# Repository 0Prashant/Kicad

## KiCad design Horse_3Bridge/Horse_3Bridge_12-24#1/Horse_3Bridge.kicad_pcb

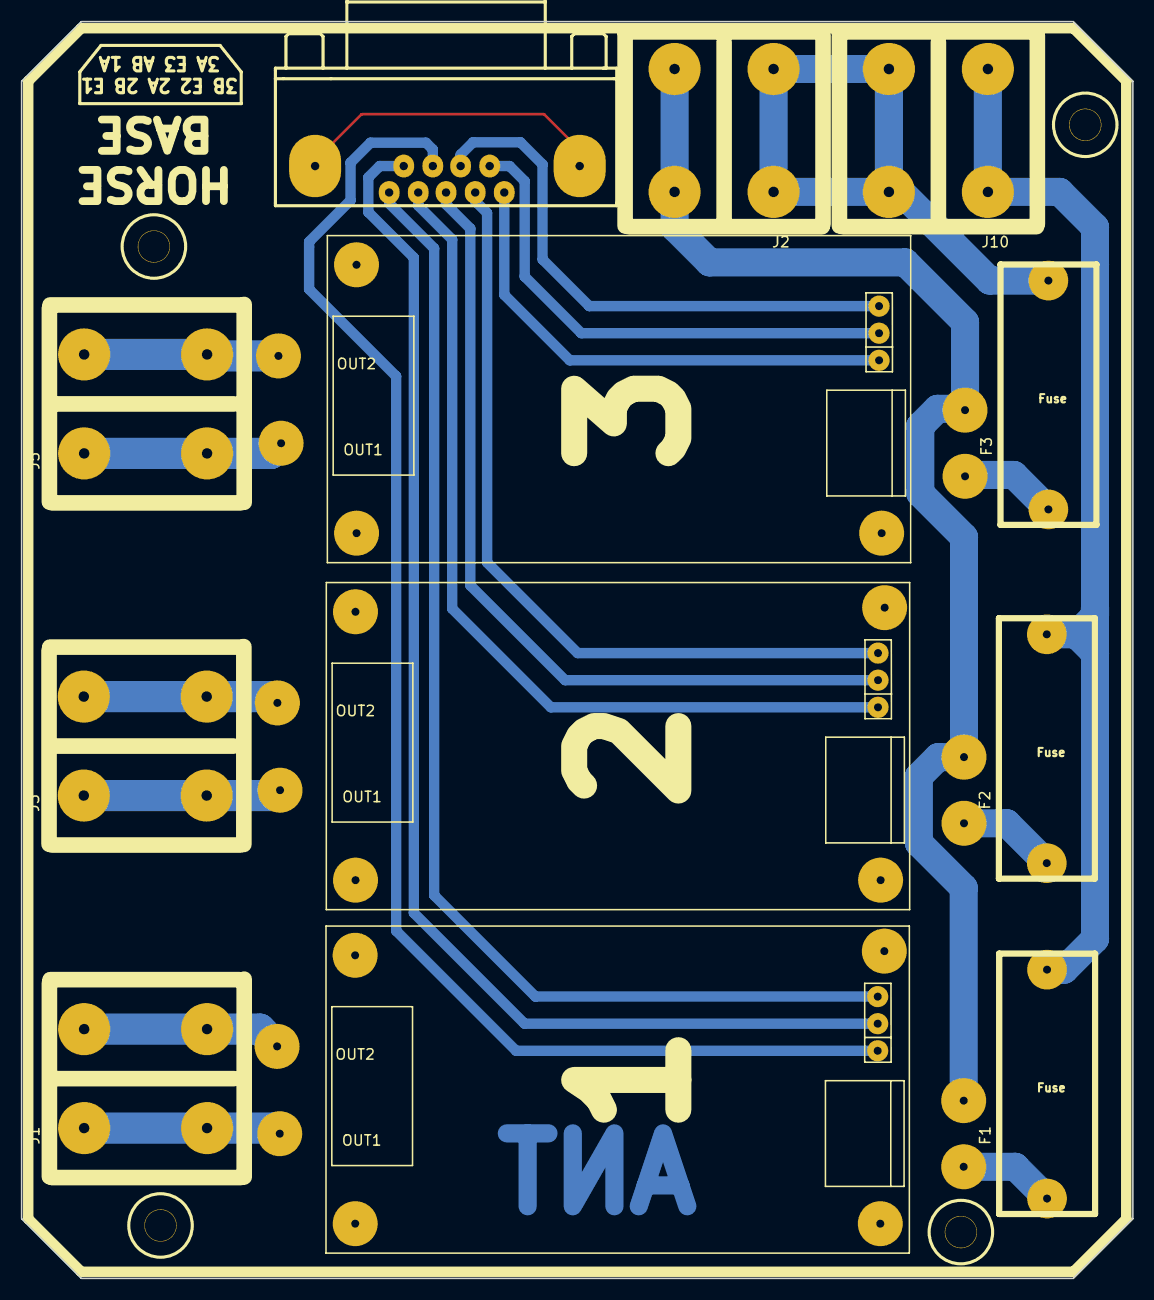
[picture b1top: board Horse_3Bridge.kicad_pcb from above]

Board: 2 copper layers, 106.7 x 120.7 mm, 16 parts (0 on the bottom side), 21 nets.

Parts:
F1, F2, F3: Fuse; Fuse_Holder
J1: M1; Solar_Connector
J2, J10: Power; Solar_Connector
J3: M2; Solar_Connector
J4: DB9_Female_MountingHoles; Connector_DB_9
J5: M3; Solar_Connector
J6, J7, J8, J9: Bolt; Nut_Bolt
U1: Motor_Driver1; H_Bridge
U2: Motor_Driver2; H_Bridge
U3: Motor_Driver3; H_Bridge

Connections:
+12V: F1.1, F2.1, J10.1
/EN1: J4.1, U1.3
/EN2: J4.4, U2.3
/EN3: J4.8, U3.3
/I1A: J4.6, U1.4
/I1B: J4.7, U1.5
/I2A: J4.3, U2.4
/I2B: J4.2, U2.5
/I3A: J4.9, U3.4
/I3B: J4.5, U3.5
/V: F3.1, J2.1, J10.2
GND: J2.2, U1.7, U2.7, U3.7
unnamed: F1.2, U1.6
unnamed: F2.2, U2.6
unnamed: F3.2, U3.6
unnamed: J1.1, U1.1
unnamed: J1.2, U1.2
unnamed: J3.1, U2.1
unnamed: J3.2, U2.2
unnamed: J5.1, U3.1
unnamed: J5.2, U3.2

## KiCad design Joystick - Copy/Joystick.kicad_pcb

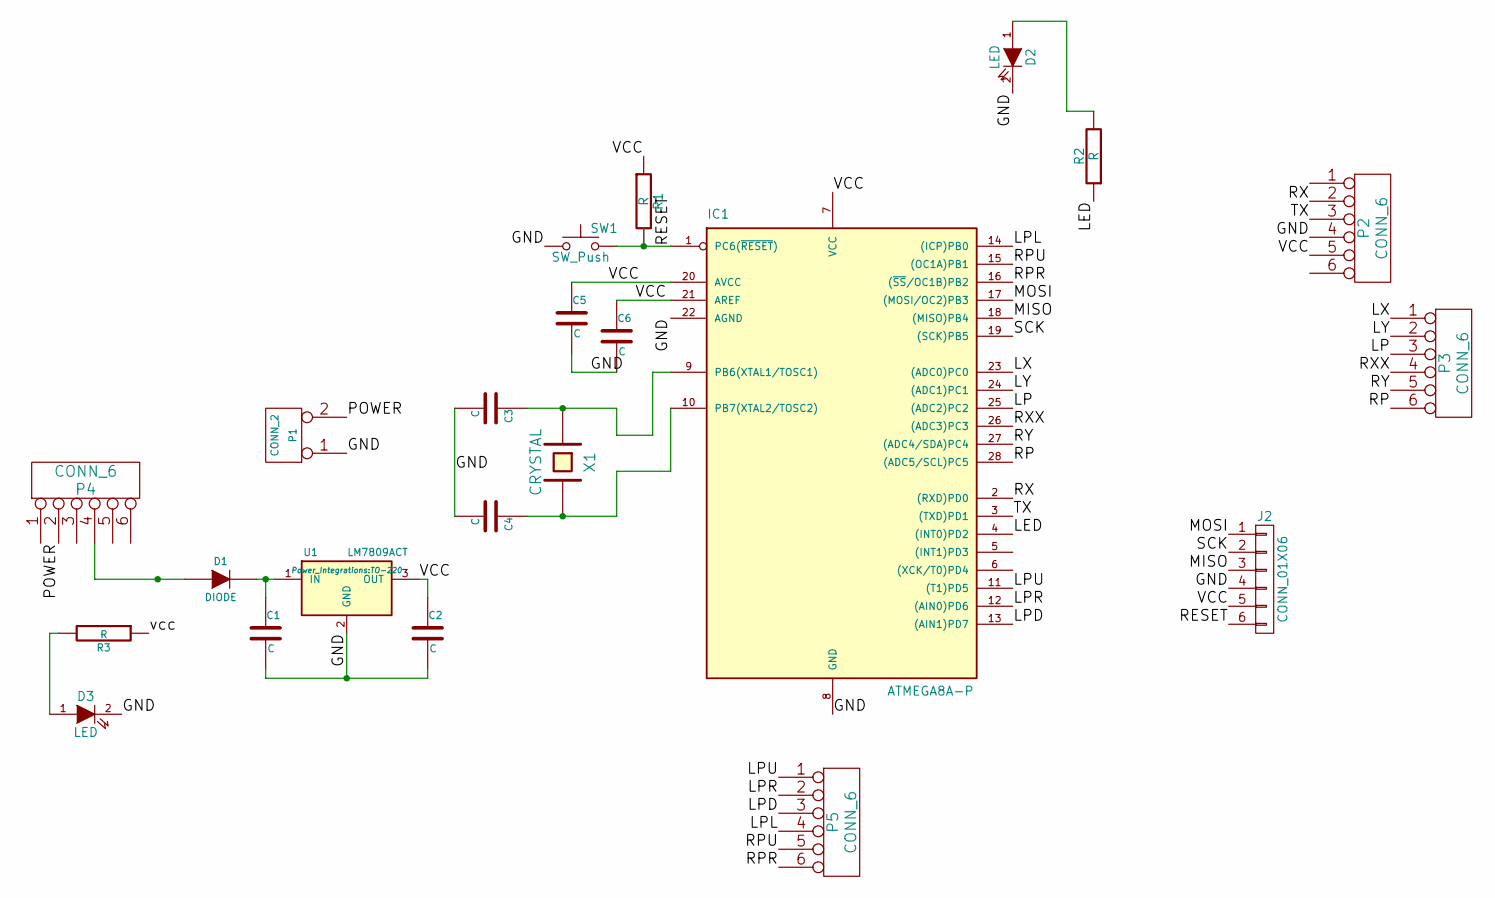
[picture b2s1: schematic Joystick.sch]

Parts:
C1: C; CP_Radial_Tantal_D4.5mm_P2.50mm
C2: C; CP_Radial_Tantal_D5.0mm_P2.50mm
C3, C4, C5, C6: C; C_Disc_D5.0mm_W2.5mm_P2.50mm
D1: DIODE; D_DO-41_SOD81_P10.16mm_Horizontal
D2, D3: LED; LED_D3.0mm
IC1: ATMEGA8A-P; DIP-28_W7.62mm
J2: CONN_01X06; Pin_Header_Straight_1x06_Pitch2.54mm
P1: CONN_2; bornier2
P2, P3, P5: CONN_6; Pin_Header_Straight_1x06_Pitch2.54mm
P4: CONN_6; Pin_Header_Straight_2x03_Pitch2.54mm
R1, R2, R3: R; R_Axial_DIN0207_L6.3mm_D2.5mm_P7.62mm_Horizontal
SW1: SW_Push; SW_PUSH_6mm_h4.3mm
U1: LM7809ACT; TO-220
X1: CRYSTAL; Crystal_HC52-8mm_Vertical

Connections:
/GND: C1.2, C2.2, C3.2, C4.2, C5.2, C6.2, D2.2 (K), D3.2 (K), IC1.8 (GND), IC1.22 (AGND), J2.4, P1.1, P2.4, SW1.1, U1.2 (GND)
/LED: IC1.4 ((INT0)PD2), R2.1
/LP: IC1.25 ((ADC2)PC2), P3.3
/LPD: IC1.13 ((AIN1)PD7), P5.3
/LPL: IC1.14 ((ICP)PB0), P5.4
/LPR: IC1.12 ((AIN0)PD6), P5.2
/LPU: IC1.11 ((T1)PD5), P5.1
/LX: IC1.23 ((ADC0)PC0), P3.1
/LY: IC1.24 ((ADC1)PC1), P3.2
/MISO: IC1.18 ((MISO)PB4), J2.3
/MOSI: IC1.17 ((MOSI/OC2)PB3), J2.1
/POWER: P1.2 (PM), P4.2
/RESET: IC1.1 (PC6(~RESET~)), J2.6, R1.2, SW1.2
/RP: IC1.28 ((ADC5/SCL)PC5), P3.6
/RPR: IC1.16 ((~SS~/OC1B)PB2), P5.6
/RPU: IC1.15 ((OC1A)PB1), P5.5
/RX: IC1.2 ((RXD)PD0), P2.2
/RXX: IC1.26 ((ADC3)PC3), P3.4
/RY: IC1.27 ((ADC4/SDA)PC4), P3.5
/SCK: IC1.19 ((SCK)PB5), J2.2
/TX: IC1.3 ((TXD)PD1), P2.3
/VCC: C2.1, C5.1, C6.1, IC1.7 (VCC), IC1.20 (AVCC), IC1.21 (AREF), J2.5, P2.5, R1.1, R3.1, U1.3 (OUT)
unnamed: C1.1, D1.2 (K), U1.1 (IN)
unnamed: C3.1, IC1.9 (PB6(XTAL1/TOSC1)), X1.1
unnamed: C4.1, IC1.10 (PB7(XTAL2/TOSC2)), X1.2
unnamed: D1.1 (A), P4.4
unnamed: D2.1 (A), R2.2
unnamed: D3.1 (A), R3.2

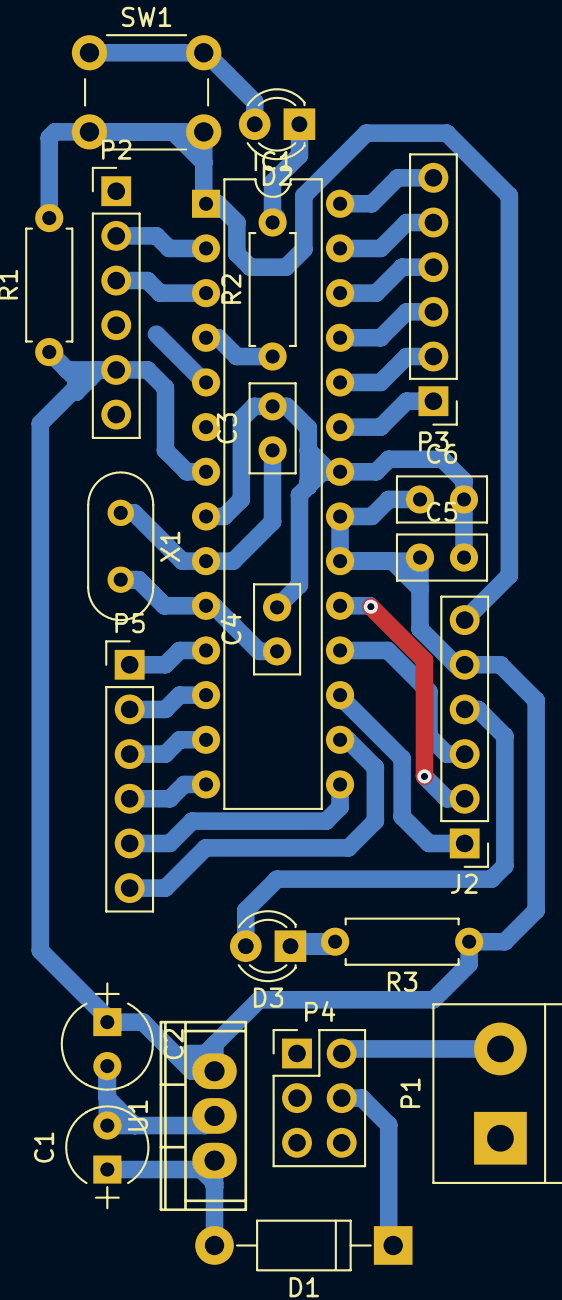
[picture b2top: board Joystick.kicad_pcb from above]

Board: 2 copper layers, 22 parts (0 on the bottom side), 28 nets.

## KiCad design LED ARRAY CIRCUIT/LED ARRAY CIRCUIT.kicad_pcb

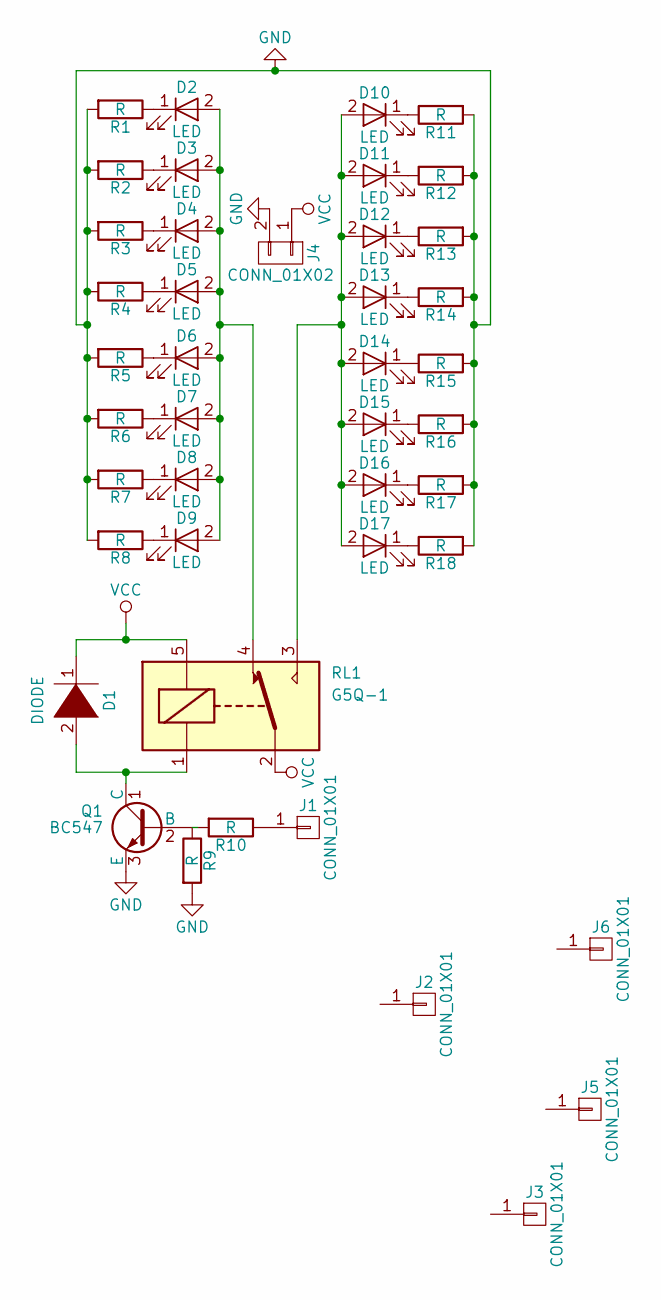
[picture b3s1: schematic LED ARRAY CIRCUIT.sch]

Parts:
D1: DIODE; Diode_Small
D2, D3, D4, D5, D6, D7, D8, D9, D10, D11, D12, D13, D14, D15, D16, D17: LED; LED_D3.0mm
J1: CONN_01X01; Pin_Header_Straight_1x01_Pitch2.00mm
J2, J3, J5, J6: CONN_01X01; 1pin
J4: CONN_01X02; Connector_Bornier_2
Q1: BC547
R1, R2, R3, R4, R5, R6, R7, R8, R9, R10, R11, R12, R13, R14, R15, R16, R17, R18: R; Resistor_small
RL1: G5Q-1; Relay_6V

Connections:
GND: J4.2, Q1.3 (E), R1.2, R2.2, R3.2, R4.2, R5.2, R6.2, R7.2, R8.2, R9.2, R11.2, R12.2, R13.2, R14.2, R15.2, R16.2, R17.2, R18.2
unnamed: D1.2 (A), Q1.1 (C), RL1.1
unnamed: D2.1 (K), R1.1
unnamed: D2.2 (A), D3.2 (A), D4.2 (A), D5.2 (A), D6.2 (A), D7.2 (A), D8.2 (A), D9.2 (A), RL1.4
unnamed: D3.1 (K), R2.1
unnamed: D4.1 (K), R3.1
unnamed: D5.1 (K), R4.1
unnamed: D6.1 (K), R5.1
unnamed: D7.1 (K), R6.1
unnamed: D8.1 (K), R7.1
unnamed: D9.1 (K), R8.1
unnamed: D10.1 (K), R11.1
unnamed: D10.2 (A), D11.2 (A), D12.2 (A), D13.2 (A), D14.2 (A), D15.2 (A), D16.2 (A), D17.2 (A), RL1.3
unnamed: D11.1 (K), R12.1
unnamed: D12.1 (K), R13.1
unnamed: D13.1 (K), R14.1
unnamed: D14.1 (K), R15.1
unnamed: D15.1 (K), R16.1
unnamed: D16.1 (K), R17.1
unnamed: D17.1 (K), R18.1
unnamed: J1.1, R10.1
unnamed: Q1.2 (B), R9.1, R10.2
VCC: D1.1 (K), J4.1, RL1.2, RL1.5

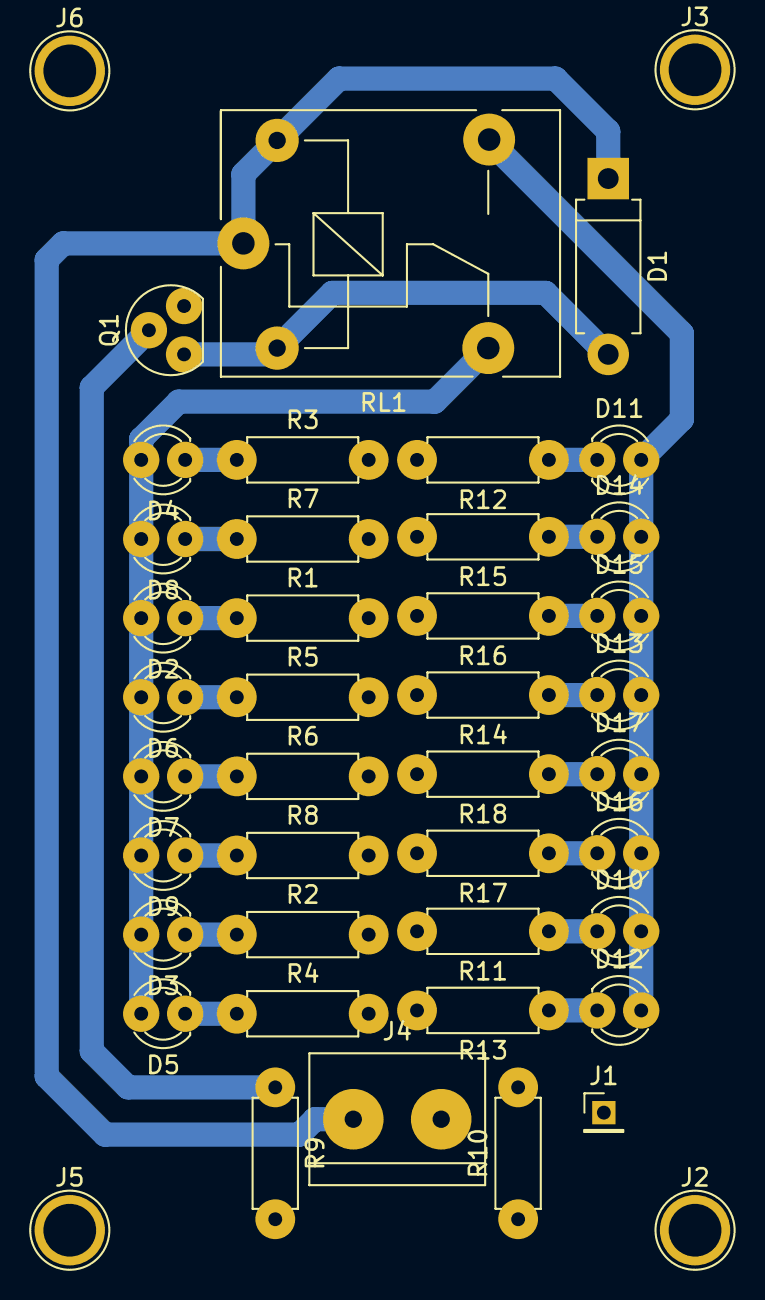
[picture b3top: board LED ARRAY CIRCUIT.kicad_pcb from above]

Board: 2 copper layers, 43 parts (0 on the bottom side), 23 nets.

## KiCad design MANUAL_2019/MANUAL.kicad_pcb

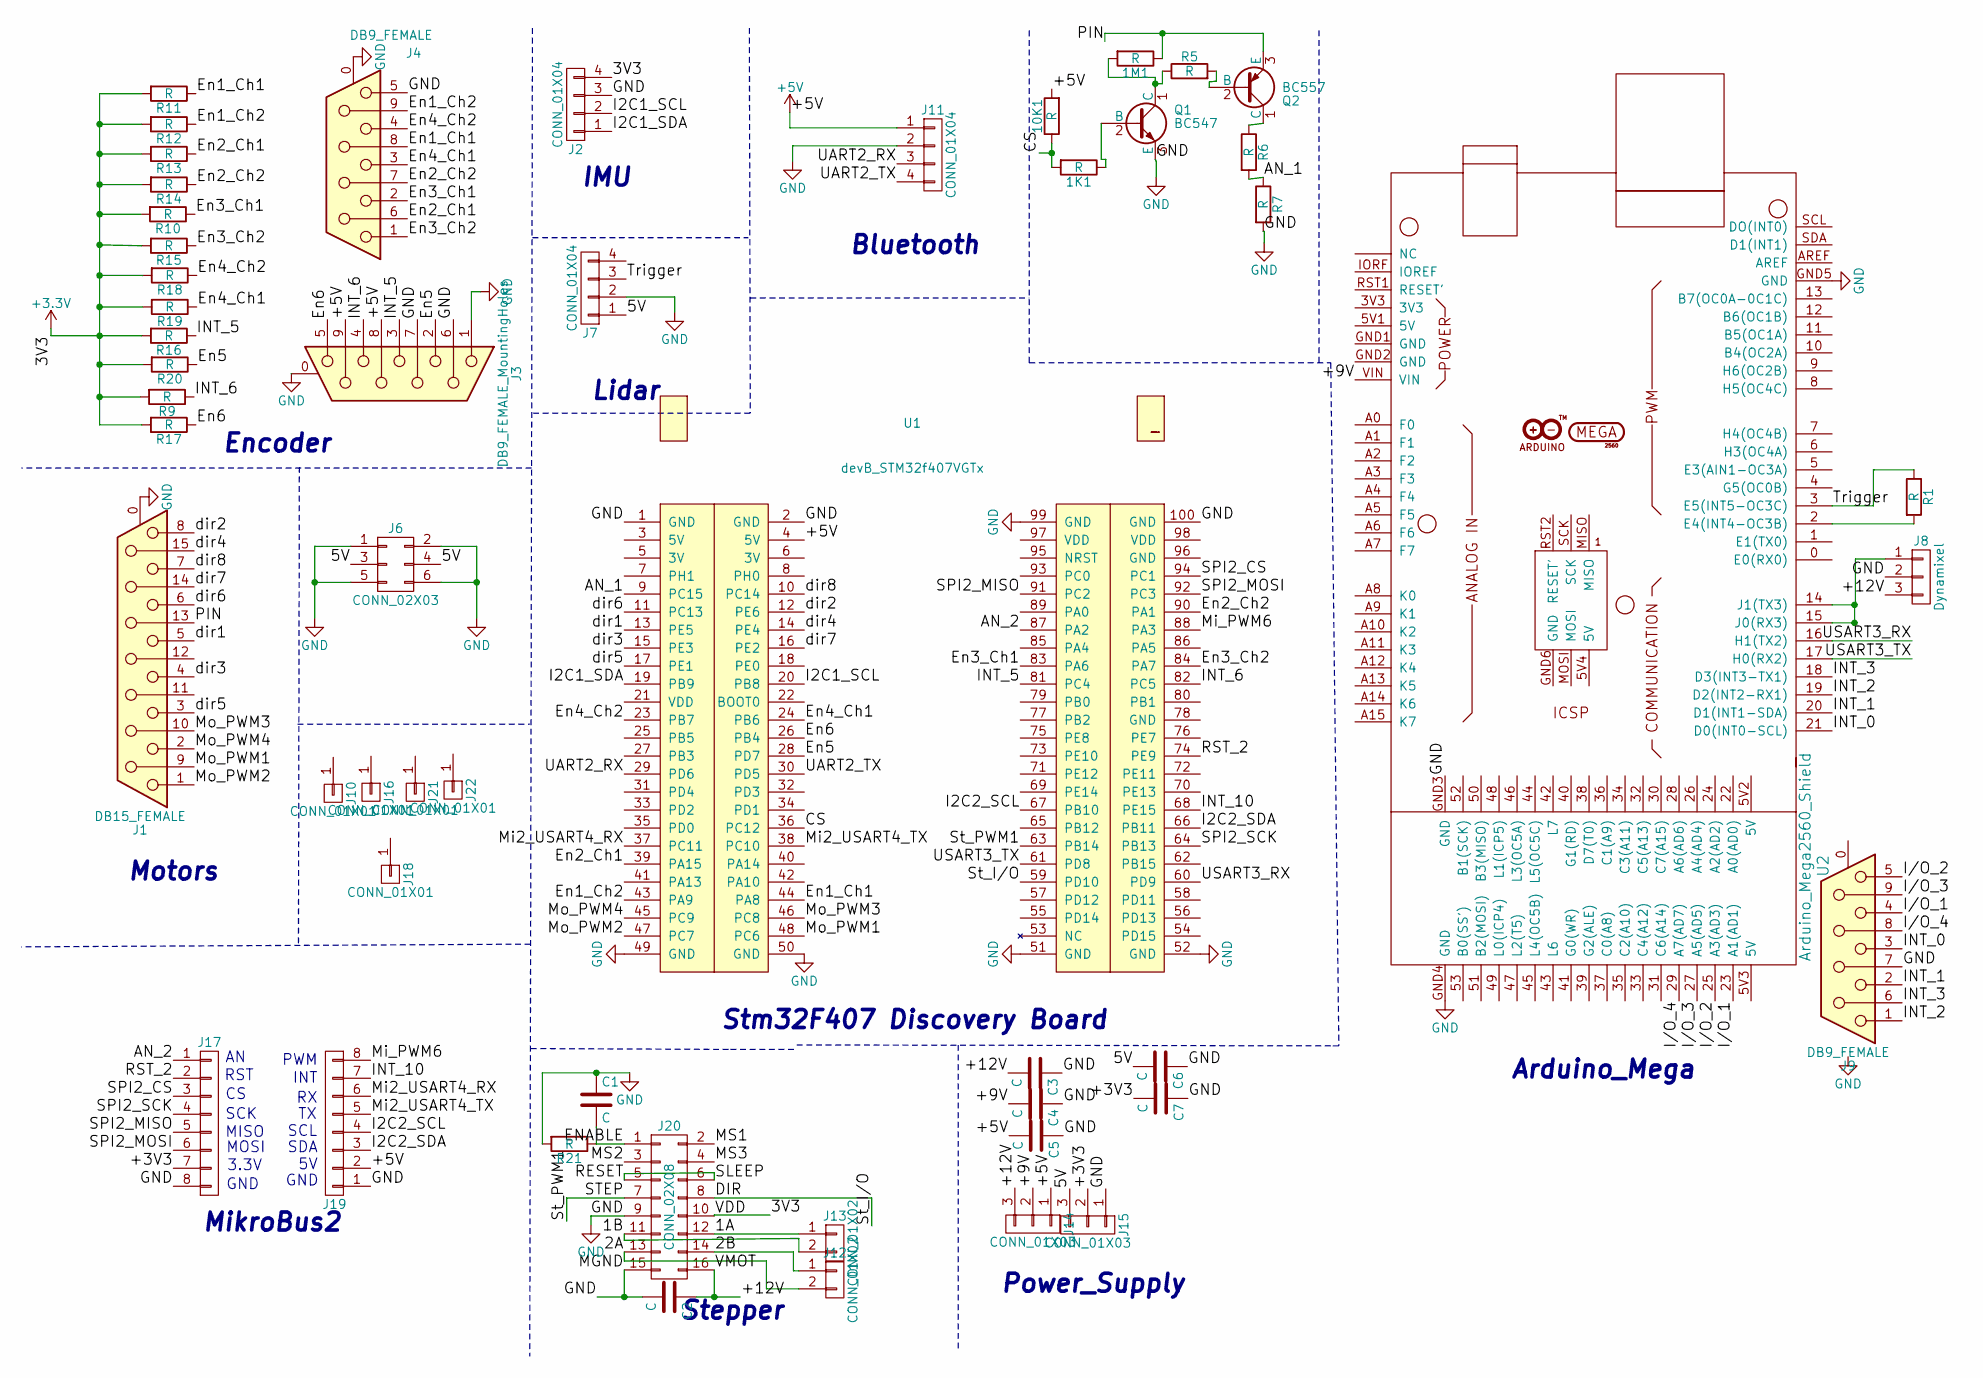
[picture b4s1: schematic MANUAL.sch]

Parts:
1K1, 1M1, 10K1: R; Resistor_small
C1: C; Capacitor_100uF
C2, C3, C4, C5, C6, C7: C; Capacitor_Disc_Small
J1: DB15_FEMALE; Connector_DB15
J2: CONN_01X04; JST_XH_B04B-XH-A_04x2.50mm_Straight
J3: DB9_FEMALE_MountingHoles; Connector_DB_9
J4, J9: DB9_FEMALE; Connector_DB_9
J6: CONN_02X03; Pin_Header_Straight_2x03_Pitch2.54mm
J7, J11: CONN_01X04; Pin_Header_Straight_1x04_Pitch2.54mm
J8: Dynamixel; TerminalBlock_Pheonix_MKDS1.5-3pol
J10, J16, J18, J21, J22: CONN_01X01; Pin_Header_Straight_1x01_Pitch2.54mm
J12, J13: CONN_01X02; TerminalBlock_Pheonix_MKDS1.5-2pol
J14, J15: CONN_01X03; TerminalBlock_Pheonix_MKDS1.5-3pol
J17, J19: CONN_01X08; Pin_Header_Straight_1x08_Pitch2.54mm
J20: CONN_02X08; A4998
Q1: BC547; TO-92_Molded_Narrow
Q2: BC557; TO-92_Molded_Narrow
R1, R5, R6, R7, R9, R10, R11, R12, R13, R14, R15, R16, R17, R18, R19, R20, R21: R; Resistor_small
U1: devB_STM32f407VGTx; STM32F407_Discovery
U2: Arduino_Mega2560_Shield

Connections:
+5V: 10K1.2, C5.2, J3.8, J3.9, J11.1, J14.1, J19.2, U1.4 (5V)
/1A: J13.1, J20.12
/1B: J13.2, J20.11
/2A: J12.2, J20.13
/2B: J12.1, J20.14
/5V: C6.2, J6.3, J6.4, J7.1, J15.3
/+9V: C4.2, J14.2, U2.VIN
/+12V: C2.1, C3.2, J8.3, J14.3, J20.16
/AN_1: R6.2, R7.1, U1.9 (PC15)
/AN_2: J17.1, U1.87 (PA2)
/CS: 1K1.2, 10K1.1, U1.36 (PC12)
/DIR: J20.8, U1.59 (PD10)
/ENABLE: C1.2, J20.1, R21.1
/En1_Ch1: J4.8, R11.1, U1.44 (PA8)
/En1_Ch2: J4.9, R12.1, U1.43 (PA9)
/En2_Ch1: J4.6, R13.1, U1.39 (PA15)
/En2_Ch2: J4.7, R14.1, U1.90 (PA1)
/En3_Ch1: J4.2, R10.1, U1.83 (PA6)
/En3_Ch2: J4.1, R15.1, U1.84 (PA7)
/En4_Ch1: J4.3, R19.1, U1.24 (PB6)
/En4_Ch2: J4.4, R18.1, U1.23 (PB7)
/En5: J3.2, R20.1, U1.28 (PD7)
/En6: J3.5, R17.1, U1.26 (PB4)
/I2C1_SCL: J2.2, U1.20 (PB8)
/I2C1_SDA: J2.1, U1.19 (PB9)
/I2C2_SCL: J19.4, U1.67 (PB10)
/I2C2_SDA: J19.3, U1.66 (PB11)
/I/O_1: J9.4, U2.23 (A1(AD1))
/I/O_2: J9.5, U2.25 (A3(AD3))
/I/O_3: J9.9, U2.27 (A5(AD5))
/I/O_4: J9.8, U2.29 (A7(AD7))
/INT_0: J9.3, U2.21 (D0(INT0-SCL))
/INT_1: J9.2, U2.20 (D1(INT1-SDA))
/INT_2: J9.1, U2.19 (D2(INT2-RX1))
/INT_3: J9.6, U2.18 (D3(INT3-TX1))
/INT_5: J3.3, R16.1, U1.81 (PC4)
/INT_6: J3.4, R9.1, U1.82 (PC5)
/INT_10: J19.7, U1.68 (PE15)
/MS1: J20.2
/MS2: J20.3
/MS3: J20.4
/Mi2_USART4_RX: J19.6, U1.37 (PC11)
/Mi2_USART4_TX: J19.5, U1.38 (PC10)
/Mi_PWM6: J19.8, U1.88 (PA3)
/Mo_PWM1: J1.9, U1.48 (PC6)
/Mo_PWM2: J1.1, U1.47 (PC7)
/Mo_PWM3: J1.10, U1.46 (PC8)
/Mo_PWM4: J1.2, U1.45 (PC9)
/PIN: 1M1.1, J1.13, Q2.3 (E)
/RESET: J20.5, J20.6
/RST_2: J17.2, U1.74 (PE9)
/SPI2_CS: J17.3, U1.94 (PC1)
/SPI2_MISO: J17.5, U1.91 (PC2)
/SPI2_MOSI: J17.6, U1.92 (PC3)
/SPI2_SCK: J17.4, U1.64 (PB13)
/STEP: J20.7, U1.63 (PB14)
/Trigger: J7.3, R1.1, U2.3 (E5(INT5-OC3C))
/UART2_RX: J11.3, U1.29 (PD6)
/UART2_TX: J11.4, U1.30 (PD5)
/USART3_RX: U1.60 (PD9), U2.16 (H1(TX2))
/USART3_TX: U1.61 (PD8), U2.17 (H0(RX2))
/dir1: J1.5, U1.13 (PE5)
/dir2: J1.8, U1.12 (PE6)
/dir3: J1.4, U1.15 (PE3)
/dir4: J1.15, U1.14 (PE4)
/dir5: J1.3, U1.17 (PE1)
/dir6: J1.6, U1.11 (PC13)
/dir7: J1.14, U1.16 (PE2)
/dir8: J1.7, U1.10 (PC14)
GND: C1.1, C2.2, C3.1, C4.1, C5.1, C6.1, C7.1, J1.0 (PAD), J2.3, J3.0 (PAD), J3.1, J3.6, J3.7, J4.0 (PAD), J4.5, J6.1, J6.2, J6.5, J6.6, J7.2, J8.2, J9.7, J11.2, J15.1, J17.8, J19.1, J20.9, J20.15, Q1.3 (E), R7.2, R21.2, U1.1 (GND), U1.2 (GND), U1.49 (GND), U1.50 (GND), U1.51 (GND), U1.52 (GND), U1.99 (GND), U1.100 (GND), U2.GND3 (GND), U2.GND4 (GND), U2.GND5 (GND)
unnamed: 1K1.1, Q1.2 (B)
unnamed: 1M1.2, Q1.1 (C), R5.1
unnamed: J8.1, U2.14 (J1(TX3)), U2.15 (J0(RX3))
unnamed: Q2.1 (C), R6.1
unnamed: Q2.2 (B), R5.2
unnamed: R1.2, U2.2 (E4(INT4-OC3B))

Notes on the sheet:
Encoder
Lidar
Bluetooth
Motors
Power_Supply
RST
SCK
MISO
MOSI
3.3V
GND
SDA
SCL
INT
PWM
MikroBus2
Stepper
Arduino_Mega
Stm32F407 Discovery Board
IMU

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
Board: 2 copper layers, 52 parts (0 on the bottom side), 74 nets, no tracks yet.
